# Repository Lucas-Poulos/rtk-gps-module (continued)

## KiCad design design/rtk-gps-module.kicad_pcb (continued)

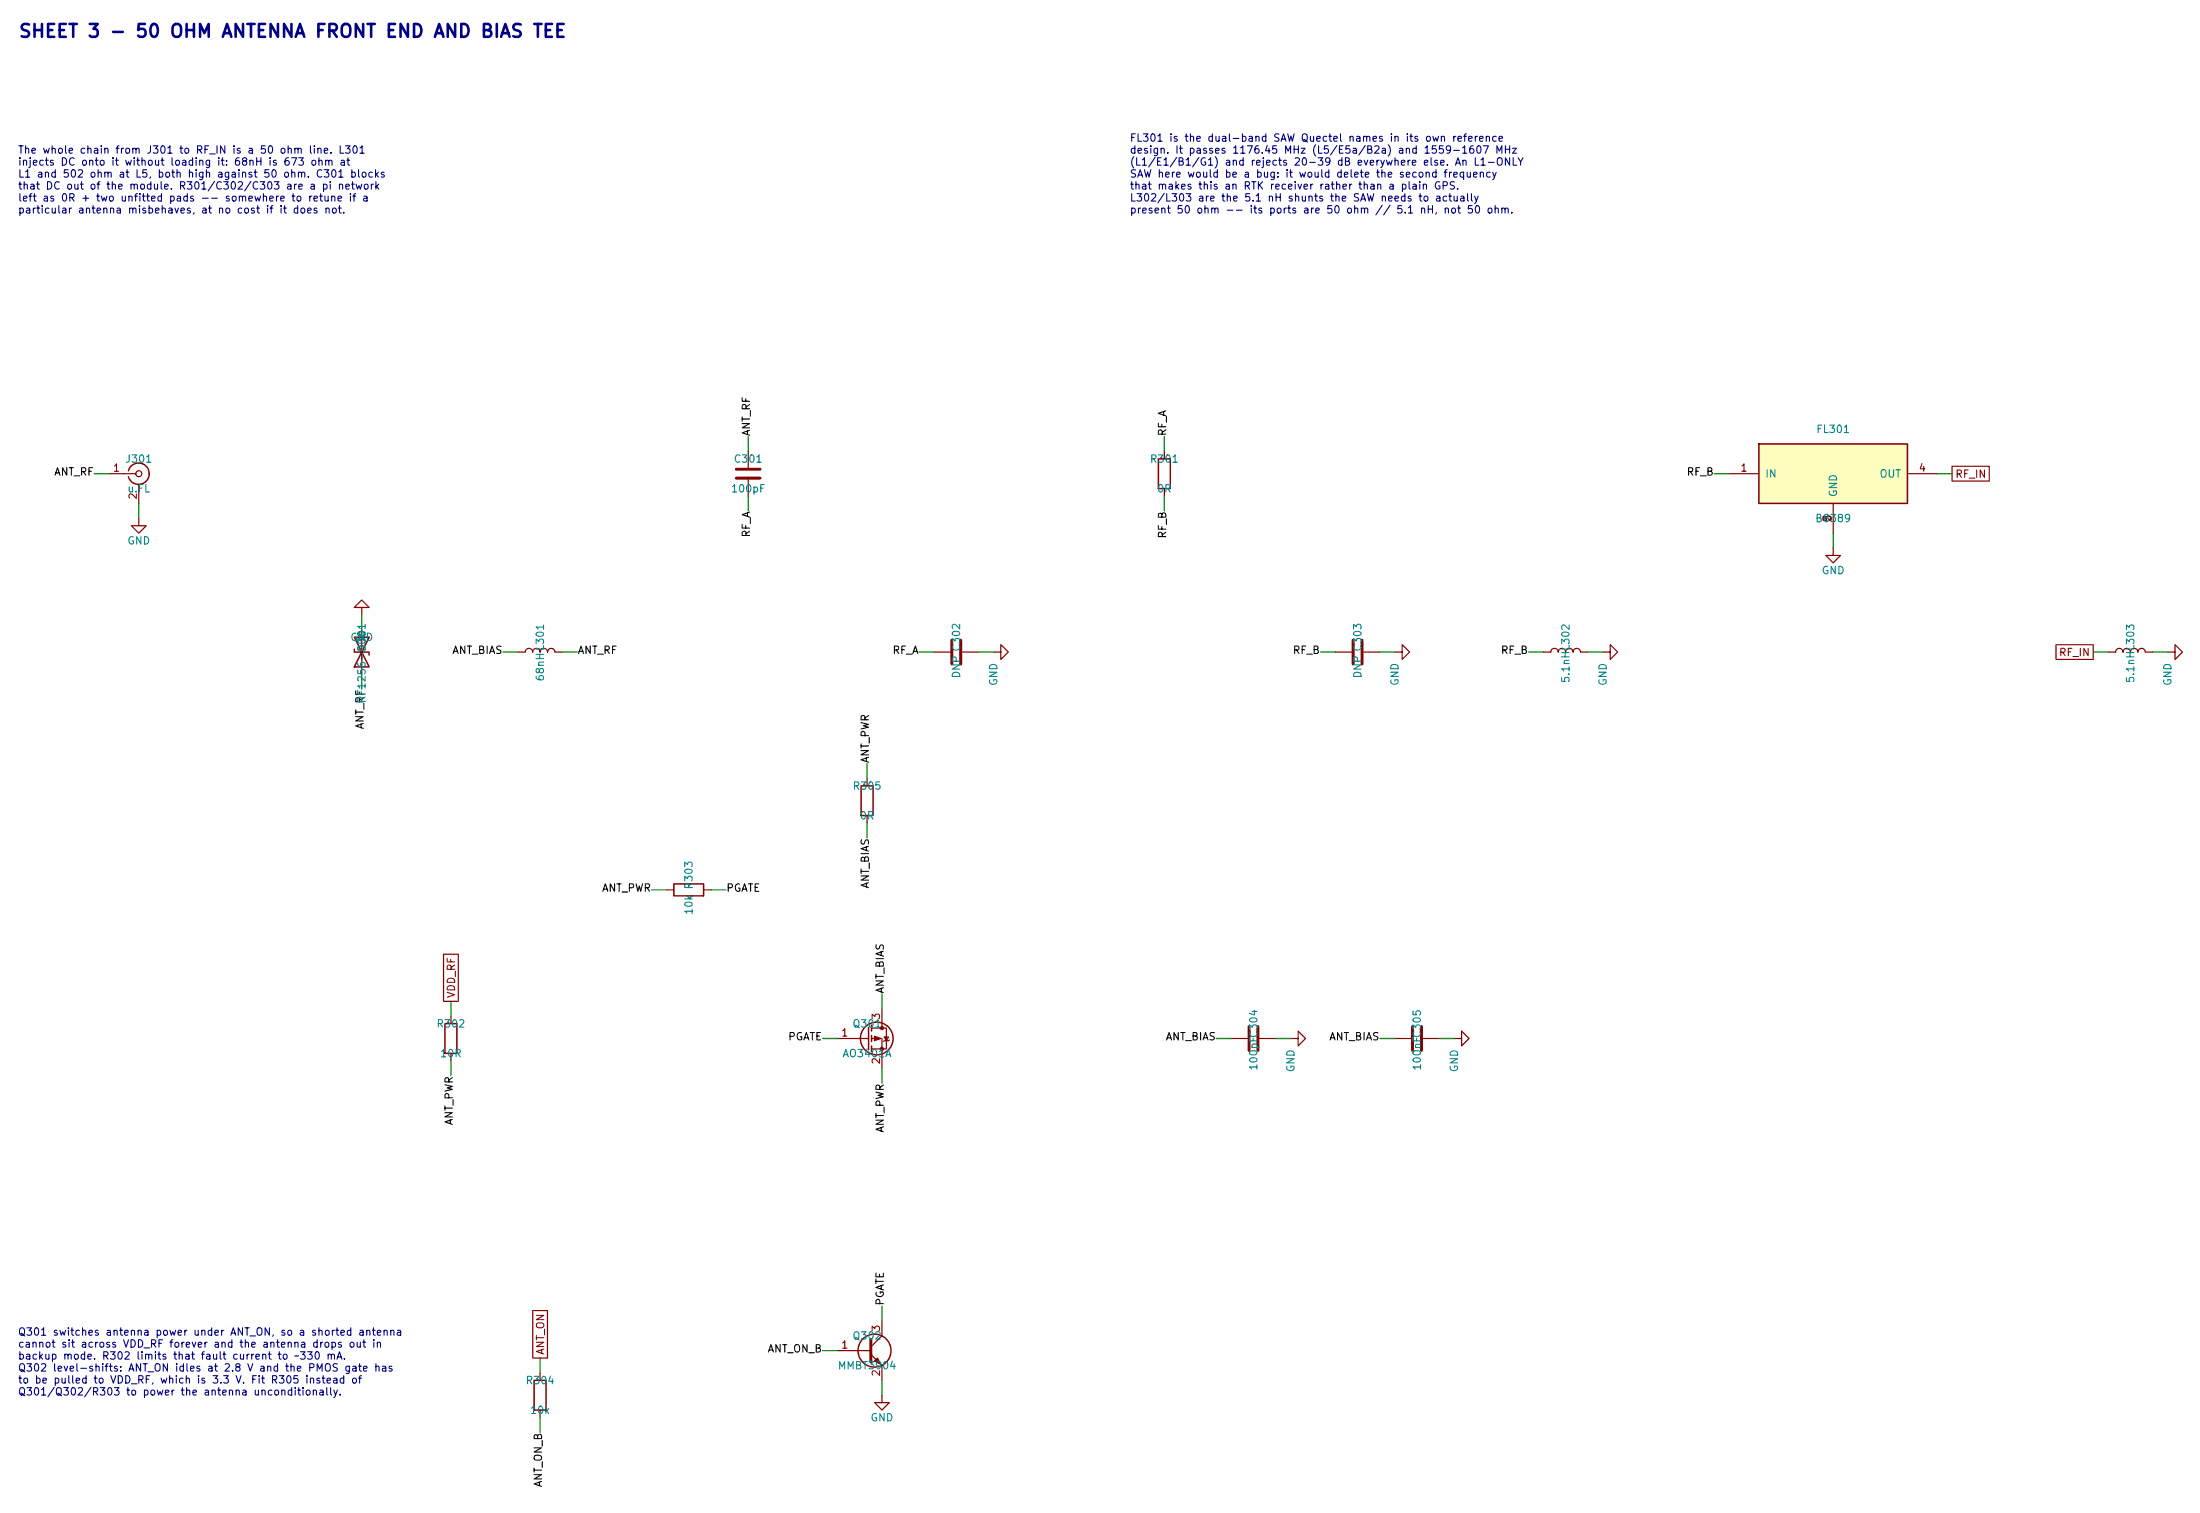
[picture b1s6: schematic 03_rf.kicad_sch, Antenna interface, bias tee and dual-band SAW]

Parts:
C301, C304: 100pF; C_0402_1005Metric; MPN 0402CG101J500NT; LCSC C1546
C302, C303: DNP; C_0402_1005Metric
C305: 100nF; C_0402_1005Metric; MPN CL05B104KO5NNNC; LCSC C1525
D301: RF1256-000; D_0603_1608Metric; MPN RF1256-000; LCSC C207186
FL301: B8389; SAW_RF360_SMD1411-5P_1.4x1.1mm; MPN B39162B8389P810; LCSC C5556161
J301: u.FL; U.FL_Hirose_U.FL-R-SMT-1_Vertical; MPN BWU.FL-IPEX1; LCSC C5137195
L301: 68nH; L_0402_1005Metric; MPN LQW15AN68NG00D; LCSC C108965
L302, L303: 5.1nH; L_0402_1005Metric; MPN LQW15AN5N1B00D; LCSC C408161
Q301: AO3401A; SOT-23; MPN AO3401A; LCSC C15127
Q302: MMBT3904; SOT-23; MPN MMBT3904; LCSC C20526
R301, R305: 0R; R_0402_1005Metric; Tolerance 1%; MPN 0402WGF0000TCE; LCSC C17168
R302: 10R; R_0402_1005Metric; Tolerance 1%; MPN 0402WGF100JTCE; LCSC C25077
R303, R304: 10k; R_0402_1005Metric; Tolerance 1%; MPN 0402WGF1002TCE; LCSC C25744

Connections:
/RF/ANT_BIAS: C304.1, C305.1, L301.1, Q301.3 (D), R305.2
/RF/ANT_ON_B: Q302.1 (B), R304.2
/RF/ANT_PWR: Q301.2 (S), R302.2, R303.1, R305.1
/RF/ANT_RF: C301.1, D301.1 (A1), J301.1 (In), L301.2
/RF/PGATE: Q301.1 (G), Q302.3 (C), R303.2
/RF/RF_A: C301.2, C302.1, R301.1
/RF/RF_B: C303.1, FL301.1 (IN), L302.1, R301.2
ANT_ON: R304.1; also elsewhere on the board
GND: C302.2, C303.2, C304.2, C305.2, D301.2 (A2), FL301.2 (GND), FL301.3 (GND), FL301.5 (GND), J301.2 (Ext), L302.2, L303.2, Q302.2 (E); also elsewhere on the board
RF_IN: FL301.4 (OUT), L303.1; also elsewhere on the board
VDD_RF: R302.1; also elsewhere on the board

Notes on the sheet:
Q301 switches antenna power under ANT_ON, so a shorted antenna cannot sit across VDD_RF forever and the antenna drops out in backup mode. R302 limits that fault current to ~330 mA. Q302 level-shifts: ANT_ON idles at 2.8 V and the PMOS gate has to be pulled to VDD_RF, which is 3.3 V. Fit R305 instea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
FL301 is the dual-band SAW Quectel names in its own reference design. It passes 1176.45 MHz (L5/E5a/B2a) and 1559-1607 MHz (L1/E1/B1/G1) and rejects 20-39 dB everywhere else. An L1-ONLY SAW here would be a bug: it would delete the second frequency that makes this an RTK receiver rather than a plain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
The whole chain from J301 to RF_IN is a 50 ohm line. L301 injects DC onto it without loading it: 68nH is 673 ohm at L1 and 502 ohm at L5, both high against 50 ohm. C301 blocks that DC out of the module. R301/C302/C303 are a pi network left as 0R + two unfitted pads -- somewhere to retune if a parti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
SHEET 3 - 50 OHM ANTENNA FRONT END AND BIAS TEE

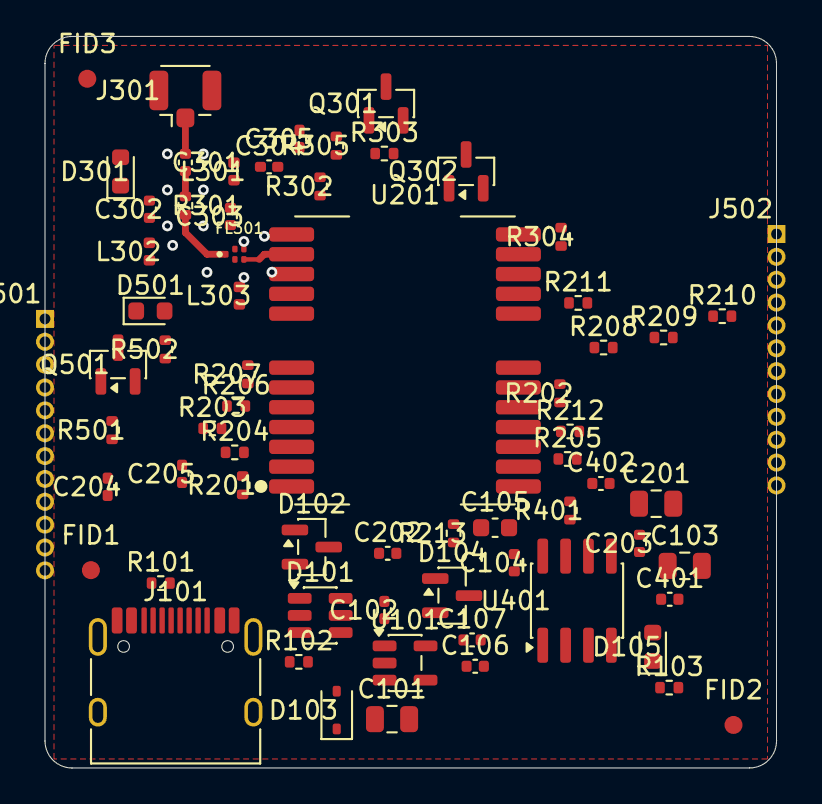
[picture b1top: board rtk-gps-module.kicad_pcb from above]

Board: 4 copper layers, 40.6 x 40.6 mm, 67 parts (0 on the bottom side), 45 nets.

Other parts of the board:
FID1, FID2, FID3: Fiducial_1mm_Mask2mm

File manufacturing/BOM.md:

# Bill of Materials

`rtk-gps-module` rev A. Generated by `tools/gen_bom.py` from the
schematic netlist -- do not edit by hand.

- **53 fitted parts** in **29 lines**
- **9 not fitted** (see `BOM-dnp.md`)
- Prices and stock read from LCSC on **2026-09-28** and frozen here for traceability. Re-check before ordering.

## Cost

| | |
|---|---|
| Parts, one board, qty-1 pricing | **$27.10** |
| of which the LC29H receiver | $23.94 (88 %) |
| of which the dual-band SAW | $1.60 |
| everything else | $1.56 |
| JLCPCB basic parts / extended | 38 / 15 |
| JLCPCB extended-part feeder fees | $39.00 one-off |

The receiver is 90 % of the bill. Nothing else on the board is worth
optimising until that changes.

## Fitted

| Qty | Refs | Value | MPN | LCSC | Pkg | Unit $ | Ext $ | Stock |
|----:|---|---|---|---|---|----:|----:|----:|
| 1 | U201 | LC29HDAMD | LC29HDAMD | [C20748061](https://www.lcsc.com/search?q=C20748061) | Quectel_LC29H_LCC-24_12.2x16.0mm | 23.9364 | 23.936 | 22 |
| 1 | FL301 | B8389 | B39162B8389P810 | [C5556161](https://www.lcsc.com/search?q=C5556161) | SAW_RF360_SMD1411-5P_1.4x1.1mm | 1.6036 | 1.604 | 130 |
| 1 | U401 | CH340N | CH340N | [C2977777](https://www.lcsc.com/search?q=C2977777) | SOIC-8_3.9x4.9mm_P1.27mm | 0.5701 | 0.570 | 14,211 |
| 3 | C101, C103, C201 | 10uF | CL21A106KAYNNNE | [C15850](https://www.lcsc.com/search?q=C15850) | C_0805_2012Metric | 0.0773 | 0.232 | 3,505,306 |
| 1 | U101 | AP2112K-3.3 | AP2112K-3.3TRG1 | [C23380830](https://www.lcsc.com/search?q=C23380830) | SOT-23-5 | 0.1089 | 0.109 | 31,470 |
| 1 | D301 | RF1256-000 | RF1256-000 | [C207186](https://www.lcsc.com/search?q=C207186) | D_0603_1608Metric | 0.0794 | 0.079 | 8,172 |
| 2 | L302, L303 | 5.1nH | LQW15AN5N1B00D | [C408161](https://www.lcsc.com/search?q=C408161) | L_0402_1005Metric | 0.0386 | 0.077 | 16,817 |
| 1 | J101 | USB-C 16P | TYPE-C 16PIN 2MD(073) | [C2765186](https://www.lcsc.com/search?q=C2765186) | USB_C_Receptacle_HRO_TYPE-C-31-M-12 | 0.0742 | 0.074 | 1,171,811 |
| 1 | Q301 | AO3401A | AO3401A | [C15127](https://www.lcsc.com/search?q=C15127) | SOT-23 | 0.0716 | 0.072 | 715,902 |
| 1 | L301 | 68nH | LQW15AN68NG00D | [C108965](https://www.lcsc.com/search?q=C108965) | L_0402_1005Metric | 0.0638 | 0.064 | 59,343 |
| 9 | C102, C104, C106, C202, C204, C205, C305, C401, C402 | 100nF | CL05B104KO5NNNC | [C1525](https://www.lcsc.com/search?q=C1525) | C_0402_1005Metric | 0.0060 | 0.054 | 16,407,331 |
| 1 | D101 | USBLC6-2SC6 | USBLC6-2SC6 | [C2827654](https://www.lcsc.com/search?q=C2827654) | SOT-23-6 | 0.0446 | 0.045 | 90,097 |
| 1 | J301 | u.FL | BWU.FL-IPEX1 | [C5137195](https://www.lcsc.com/search?q=C5137195) | U.FL_Hirose_U.FL-R-SMT-1_Vertical | 0.0398 | 0.040 | 704,735 |
| 1 | D103 | SD05 | SD05 | [C502527](https://www.lcsc.com/search?q=C502527) | D_SOD-323 | 0.0305 | 0.030 | 858,741 |
| 1 | C105 | 4.7uF | CL10A475KO8NNNC | [C19666](https://www.lcsc.com/search?q=C19666) | C_0603_1608Metric | 0.0236 | 0.024 | 1,373,603 |
| 2 | Q302, Q501 | MMBT3904 | MMBT3904 | [C20526](https://www.lcsc.com/search?q=C20526) | SOT-23 | 0.0108 | 0.022 | 2,033,567 |
| 2 | C301, C304 | 100pF | 0402CG101J500NT | [C1546](https://www.lcsc.com/search?q=C1546) | C_0402_1005Metric | 0.0078 | 0.016 | 266,701 |
| 2 | D102, D104 | BAT54C | BAT54C | [C916424](https://www.lcsc.com/search?q=C916424) | SOT-23 | 0.0072 | 0.014 | 1,002,652 |
| 1 | D501 | GREEN 1PPS | KT-0603G | [C12624](https://www.lcsc.com/search?q=C12624) | LED_0603_1608Metric | 0.0122 | 0.012 | 366,908 |
| 2 | C107, C203 | 33pF | 0402CG330J500NT | [C1562](https://www.lcsc.com/search?q=C1562) | C_0402_1005Metric | 0.0049 | 0.010 | 690,617 |
| 1 | D105 | RED | KT-0603R | [C2286](https://www.lcsc.com/search?q=C2286) | LED_0603_1608Metric | 0.0073 | 0.007 | 8,154,450 |
| 6 | R201, R204, R212, R303, R304, R501 | 10k | 0402WGF1002TCE | [C25744](https://www.lcsc.com/search?q=C25744) | R_0402_1005Metric | 0.0005 | 0.003 | 20,674,699 |
| 3 | R103, R205, R502 | 1k | 0402WGF1001TCE | [C11702](https://www.lcsc.com/search?q=C11702) | R_0402_1005Metric | 0.0005 | 0.002 | 12,617,545 |
| 2 | R301, R401 | 0R | 0402WGF0000TCE | [C17168](https://www.lcsc.com/search?q=C17168) | R_0402_1005Metric | 0.0005 | 0.001 | 18,421,967 |
| 2 | R101, R102 | 5.1k | 0402WGF5101TCE | [C25905](https://www.lcsc.com/search?q=C25905) | R_0402_1005Metric | 0.0004 | 0.001 | 8,446,095 |
| 1 | R213 | 22R | 0402WGF220JTCE | [C25092](https://www.lcsc.com/search?q=C25092) | R_0402_1005Metric | 0.0006 | 0.001 | 4,094,909 |
| 1 | R202 | 100k | 0402WGF1003TCE | [C25741](https://www.lcsc.com/search?q=C25741) | R_0402_1005Metric | 0.0005 | 0.001 | 15,436,416 |
| 1 | R203 | 4.7k | 0402WGF4701TCE | [C25900](https://www.lcsc.com/search?q=C25900) | R_0402_1005Metric | 0.0005 | 0.000 | 9,379,077 |
| 1 | R302 | 10R | 0402WGF100JTCE | [C25077](https://www.lcsc.com/search?q=C25077) | R_0402_1005Metric | 0.0005 | 0.000 | 4,398,696 |

## Notes

- **LC29HDAMD** (`C20748061`, U201) -- THE cost and THE stock risk. LC29HBS (C21385845, RTK base) and LC29HAA (C22403415, no RTK engine) share the footprint
- **B39162B8389P810** (`C5556161`, FL301) -- dual-band L1+L5. Do NOT substitute an L1-only SAW -- it deletes the second band RTK depends on
- **LQW15AN5N1B00D** (`C408161`, L302, L303) -- 5.1nH is the SAW's specified port match, not a rounding of 5nH
- **LQW15AN68NG00D** (`C108965`, L301) -- wirewound, >=68nH per the Quectel reference. A ferrite bead here would eat the antenna signal
- **RF1256-000** (`C207186`, D301) -- 0.25pF junction capacitance. The LC29H guide caps this at 0.6pF -- an ordinary ESD diode detunes the antenna

## Not purchased

Board features that carry a footprint but nothing to order.

- `J501` LEFT EDGE -- Castellated_1x12_P1.27mm
- `J502` RIGHT EDGE -- Castellated_1x12_P1.27mm

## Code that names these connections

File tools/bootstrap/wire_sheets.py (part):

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USB_DM = "USB_DM"
UART_TX = "UART_TX"      # receiver -> host (NMEA / PQTM out)
RX_BUS = "RX_BUS"        # host -> receiver (RTCM3 in), before the divider
RXD1_NET = "RXD1_NET"    # after the divider, at the module pin
PPS = "PPS"
RESET_N = "RESET_N"
WAKEUP = "WAKEUP"
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    # a driver. 3V3 does -- the LDO's VOUT is a power_out.
    flag_port(w, GND, 60, 265)
    flag_label(w, VBUS, 100, 265)
    flag_label(w, VSYS, 140, 265)
    flag_label(w, V_BCKP, 180, 265)


# ==========================================================================
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# links. Pads 5-8 on the right edge are NOT 3.3 V tolerant.

J501_MAP = [
    ("Pin_1", GND), ("Pin_2", VEXT_5V), ("Pin_3", V3V3),
    ("Pin_4", VBCKP_EXT), ("Pin_5", GND), ("Pin_6", UART_TX),
    ("Pin_7", RX_BUS), ("Pin_8", PPS), ("Pin_9", RESET_N),
    ("Pin_10", WAKEUP), ("Pin_11", VDD_EXT), ("Pin_12", GND),
]

J502_MAP = [
    ("Pin_1", GND), ("Pin_2", ANT_ON), ("Pin_3", SDA_PAD),
    ("Pin_4", SCL_PAD), ("Pin_5", TXD2_PAD), ("Pin_6", RXD2_PAD),
    ("Pin_7", D_SEL1), ("Pin_8", D_SEL2), ("Pin_9", GND),
    ("Pin_10", None), ("Pin_11", None), ("Pin_12", GND),
]

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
